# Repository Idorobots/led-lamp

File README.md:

LED lamp
--------

A fairly basic desk lamp with power-led driver circuit.

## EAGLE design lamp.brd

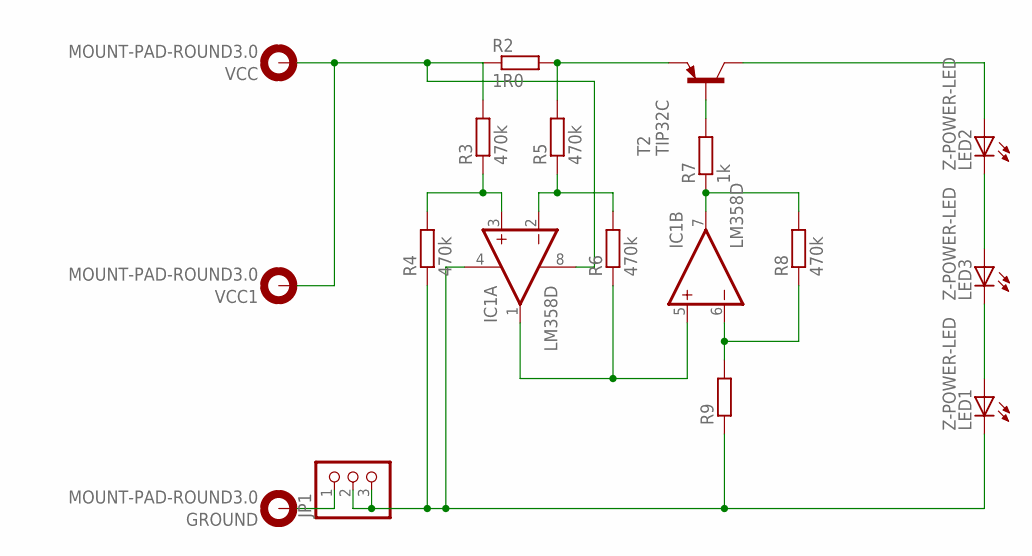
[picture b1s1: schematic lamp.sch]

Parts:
GROUND: MOUNT-PAD-ROUND3.0; 3,0-PAD
IC1: LM358D; SO08
JP1: PINHD-1X3; 1X03
LED1, LED2, LED3: Z-POWER-LED; Z-POWER-LED-PCB-TYPE
R2: 1R0; R1210
R3, R4, R5, R6, R8: 470k; R1206
R7: 1k; R1206
R9: R-EU_R1206; R1206
T2: TIP32C; TO220
VCC, VCC1: MOUNT-PAD-ROUND3.0; 3,0-PAD

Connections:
GND: IC1.4 (V-), JP1.2, JP1.3, LED1.C, R4.1, R9.1
unnamed: R2.2, R5.2, T2.3 (E)
unnamed: R7.2, T2.1 (B)
unnamed: IC1.7 (OUT), R7.1, R8.2
unnamed: LED2.A, T2.2 (C)
unnamed: LED2.C, LED3.A
unnamed: LED1.A, LED3.C
unnamed: IC1.1 (OUT), IC1.5 (+IN), R6.1
unnamed: IC1.6 (-IN), R8.1, R9.2
unnamed: IC1.3 (+IN), R3.1, R4.2
unnamed: IC1.2 (-IN), R5.1, R6.2
unnamed: GROUND.B3,0, JP1.1
VCC: IC1.8 (V+), R2.1, R3.2, VCC.B3,0, VCC1.B3,0

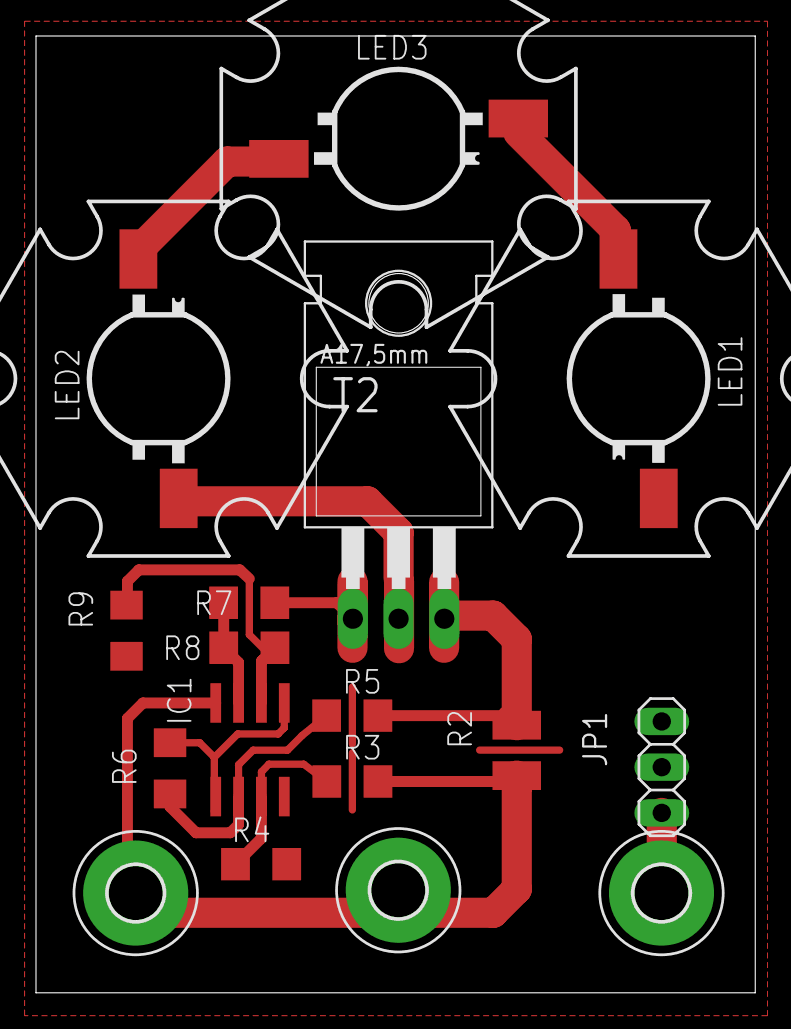
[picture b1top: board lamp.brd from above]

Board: 2 copper layers, 40.0 x 53.2 mm, 17 parts (0 on the bottom side), 13 nets.

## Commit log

2015-12-03 Save untracked version
2015-12-04 Updated the LED lamp schematic.
2015-12-04 Updated the PCB layout.
2015-12-04 Adjusted LED placement on the PCB.
2015-12-05 Whoops...
    Swapped pins in the schematic, so gotta redo the entire PCB layout.
2015-12-05 Improved the design.
2015-12-05 Added .gitignore.
2015-12-05 Added a README.
2015-12-08 Adjusted resistor values & packages.
2015-12-08 Redesigned the PCB to accomodate the SMD shunt.
2015-12-08 Added a power switch.
2015-12-08 Added another mounting hole & removed the potentiometer.
2015-12-08 Adjusted label placement.
2015-12-08 Removed the project file.
